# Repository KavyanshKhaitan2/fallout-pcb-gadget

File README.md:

# Fallout PCB Gadget!!!
This is a project for Day 2 of Fallout!!!

This is just a cool keychain that spells out "Hi!"

## BOM
| Sl. | Part name           | Qty |
|-----|---------------------|-----|
|  1. | 3V coin cell holder |   2 |
|  2. | 3mm LEDs            | 19  |
|  3. | SS-12F23-G4 Switch  |   1 |
|  4. | PCB                 |   1 |

## PCB

## Schematic

## 3D View

## What is my slack username?
Oh! I am Kavyansh Khaitan (@kavyansh.) on the Slack!!!

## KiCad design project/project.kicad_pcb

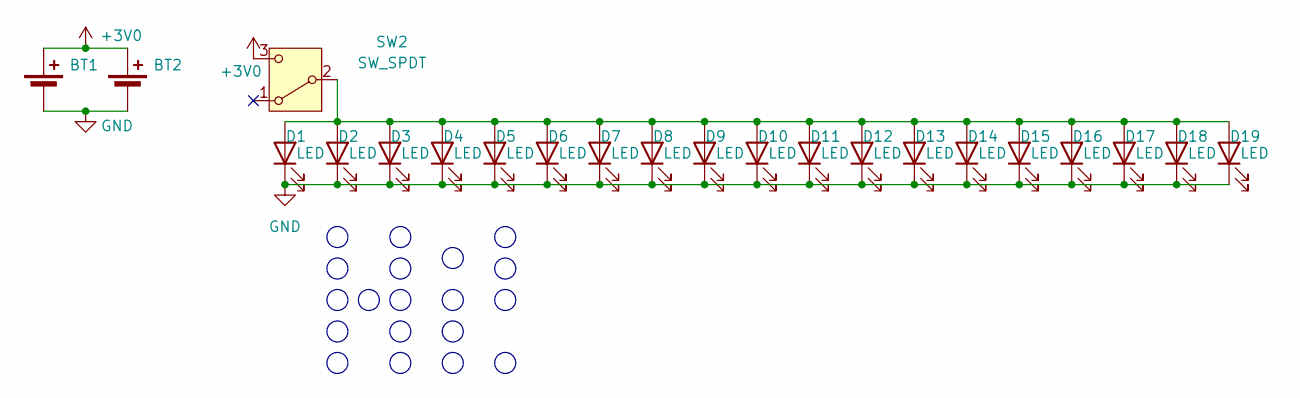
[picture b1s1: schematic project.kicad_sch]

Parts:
BT1, BT2: Battery_Cell; BatteryHolder_Keystone_3034_1x20mm
D1, D2, D3, D4, D5, D6, D7, D8, D9, D10, D11, D12, D13, D14, D15, D16, D17, D18, D19: LED; LED_D3.0mm
SW2: SW_SPDT; SW-TH_SS-12F23-G040

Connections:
+3V0: BT1.1 (+), BT2.1 (+), SW2.3 (C)
GND: BT1.2 (-), BT2.2 (-), D1.1 (K), D2.1 (K), D3.1 (K), D4.1 (K), D5.1 (K), D6.1 (K), D7.1 (K), D8.1 (K), D9.1 (K), D10.1 (K), D11.1 (K), D12.1 (K), D13.1 (K), D14.1 (K), D15.1 (K), D16.1 (K), D17.1 (K), D18.1 (K), D19.1 (K)
unnamed: D1.2 (A), D2.2 (A), D3.2 (A), D4.2 (A), D5.2 (A), D6.2 (A), D7.2 (A), D8.2 (A), D9.2 (A), D10.2 (A), D11.2 (A), D12.2 (A), D13.2 (A), D14.2 (A), D15.2 (A), D16.2 (A), D17.2 (A), D18.2 (A), D19.2 (A), SW2.2 (B)

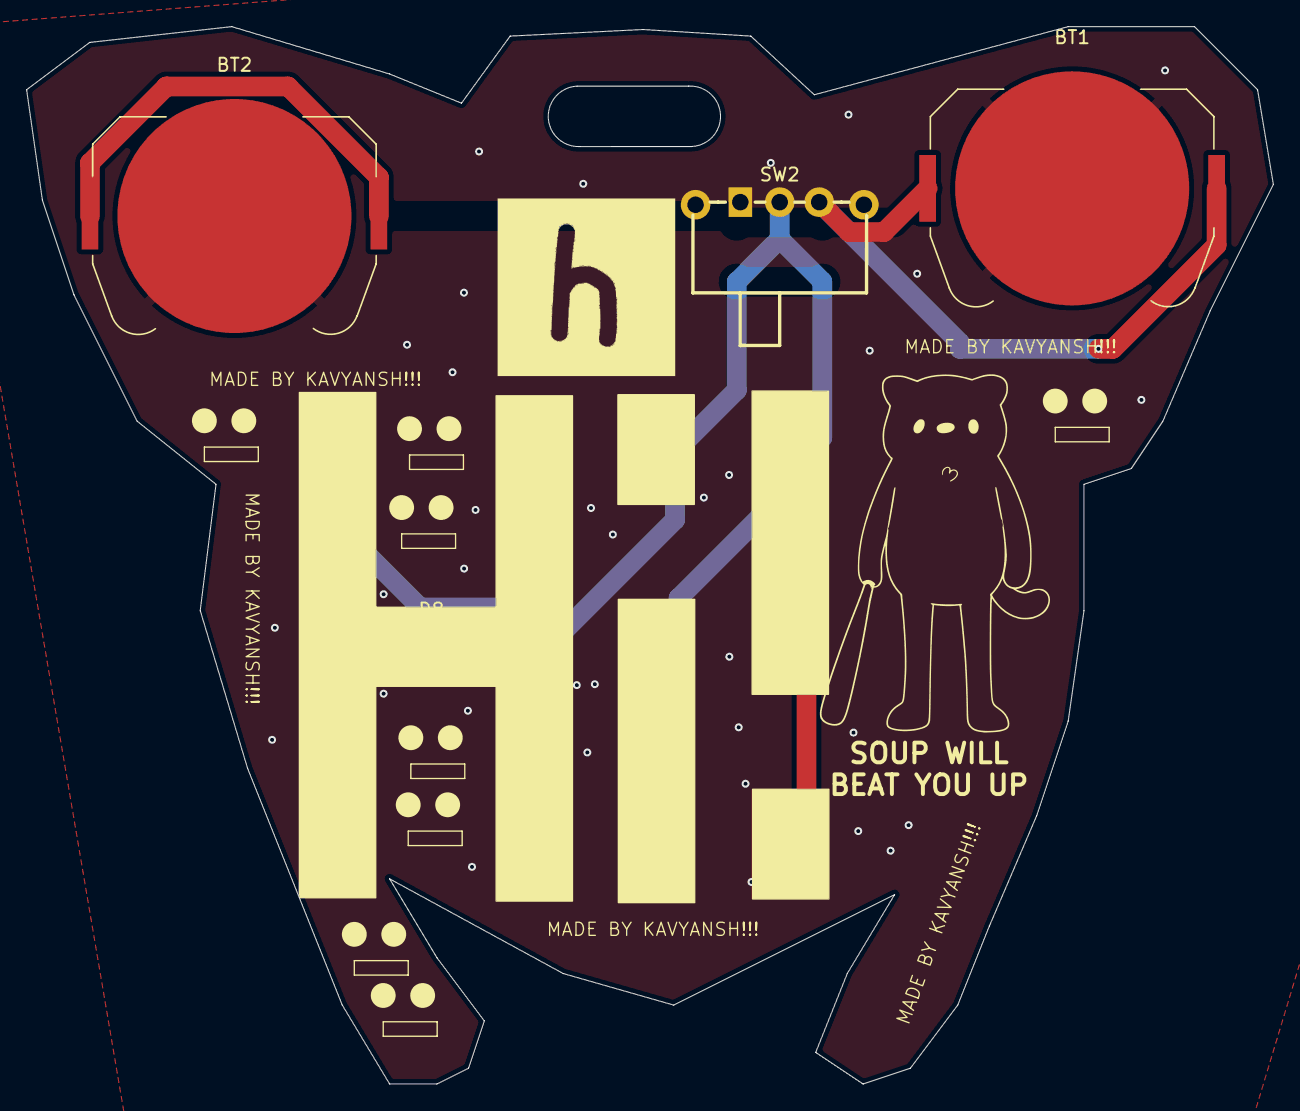
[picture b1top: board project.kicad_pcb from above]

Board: 2 copper layers, 94.8 x 80.4 mm, 22 parts (0 on the bottom side), 3 nets.

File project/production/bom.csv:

Designator,Footprint,Quantity,Value,LCSC Part #
"BT1, BT2",BatteryHolder_Keystone_3034_1x20mm,2,Battery_Cell,
"D1, D10, D11, D12, D13, D14, D15, D16, D17, D18, D19, D2, D3, D4, D5, D6, D7, D8, D9",LED_D3.0mm,19,LED,
SW1,SW_PUSH_6mm,1,SW_Push,
